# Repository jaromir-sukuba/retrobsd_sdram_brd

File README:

SDRAM board for RetroBSD
http://retrobsd.org/wiki/doku.php
http://retrobsd.org/viewtopic.php?f=3&t=5004

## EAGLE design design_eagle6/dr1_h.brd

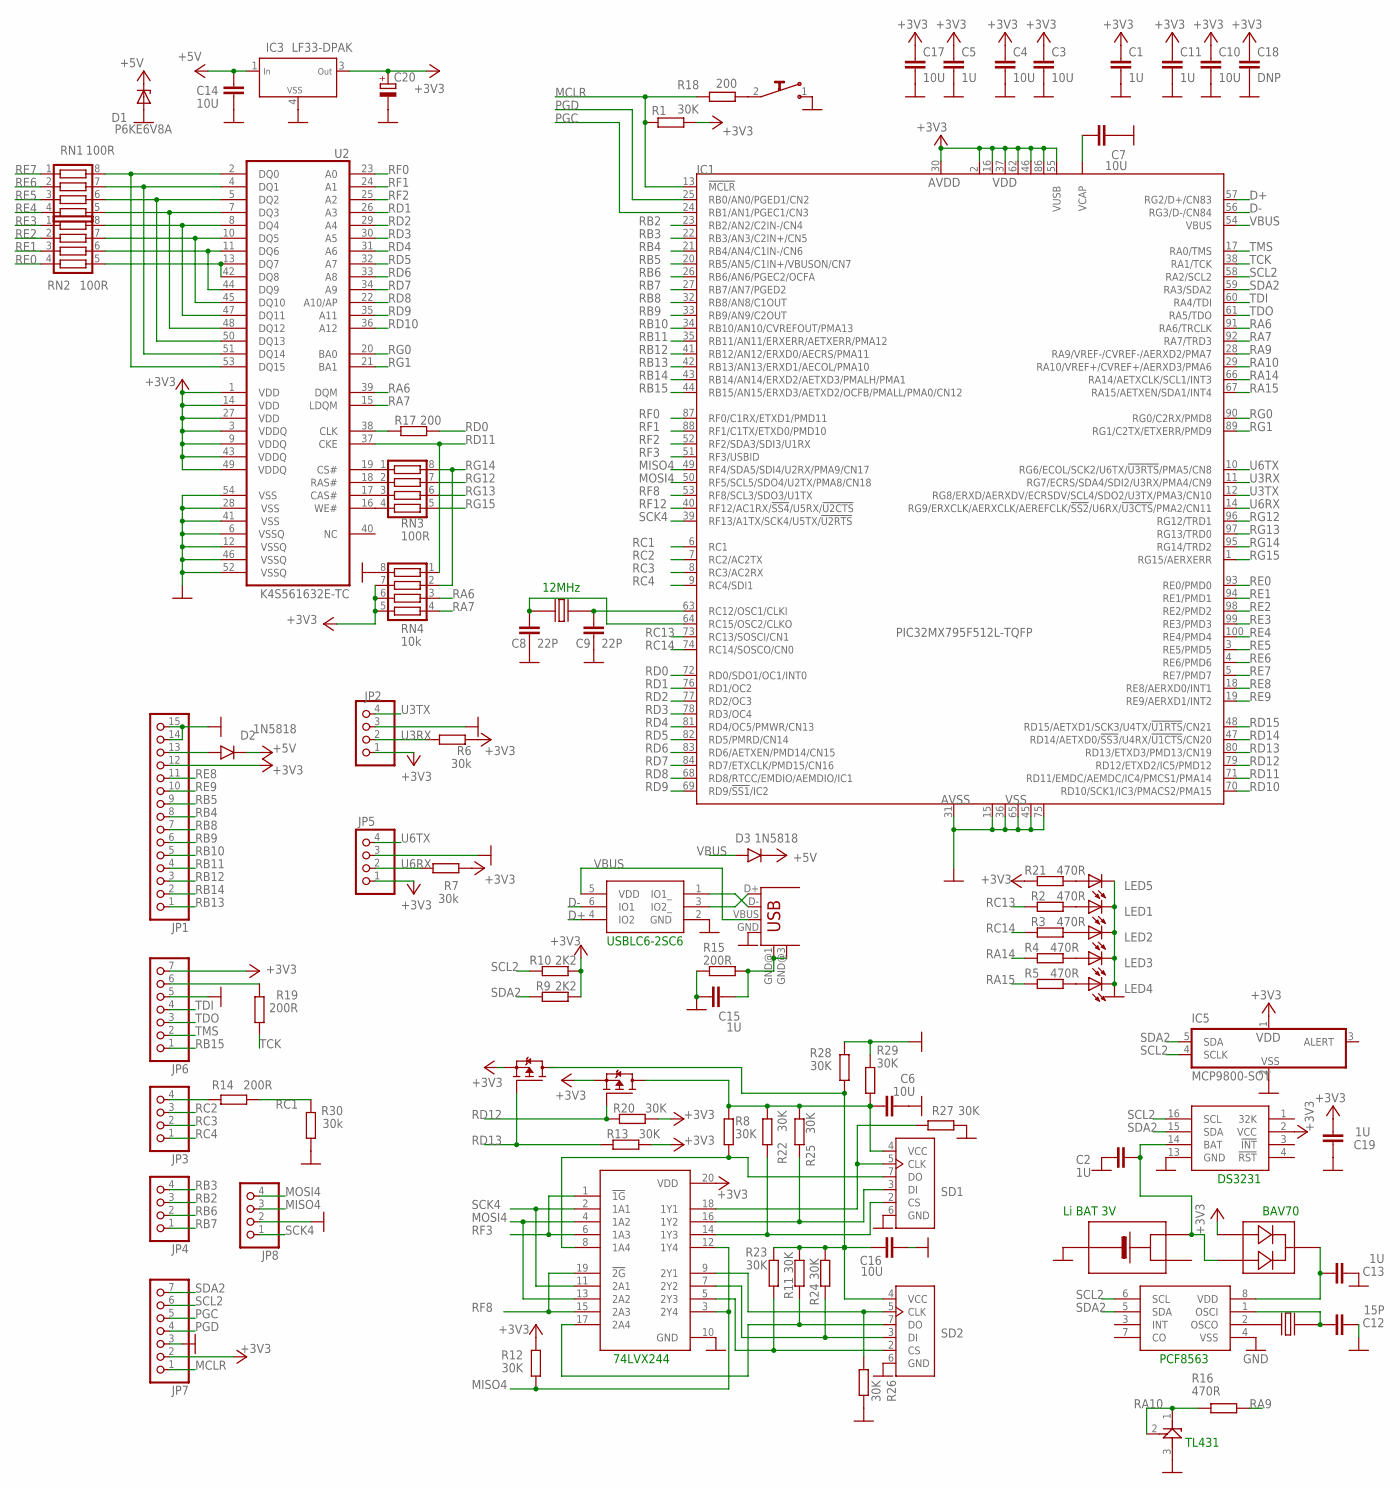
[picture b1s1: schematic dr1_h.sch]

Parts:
1: WE_TVS_2USB; SOT23-6
B1: BATT_3001; BATT_KEYS3001
C1, C2, C5, C11, C13: 1U; R0805
C3, C4, C6, C7, C10, C14, C16, C17: 10U; R0805
C8, C9: 22P; 0603
C12: 15P; R0805
C15, C19: 1U; 0603
C18: DNP; R0805
C20: CPOL-EUSMCB; SMC_B
D1: P6KE6V8A; SMB
D2, D3: 1N5818; SM-1
IC1: PIC32MX795F512L-TQFP; TQFP100
IC2: 74244TSSOP20; TSSOP20
IC3: LF33-DPAK; DPAK
IC4: PCF8563_SO8; SO-08
IC5: MCP9800-SOT; SOT23-5L
JP1: PINHD-1X15_2.54-S; 1X15-S
JP2, JP3, JP4, JP5, JP8: PINHD-1X04_2.54-S; 1X04-S
JP6, JP7: PINHD-1X07_2.54-S; 1X07-S
LED1, LED2, LED3, LED4, LED5: LEDCHIPLED_0603; CHIPLED_0603
R1, R8, R11, R12, R13, R20, R22, R23, R24, R25, R26, R27, R28, R29: 30K; 0603
R2, R3, R4, R5, R16, R21: 470R; 0603
R6, R7, R30: 30k; 0603
R9, R10: 2K2; 0603
R14, R15, R19: 200R; 0603
R17, R18: 200; 0603
RN1, RN2, RN3: 100R; CTS742C083
RN4: 10k; CTS742C083
SD1, SD2: SF-MICROSD; MICROSD
T1: SI2333; SOT23-3
U2: K4S561632E-TC; TSOP54
U$1: TL431_SOT23; SOT23
U$2: DS3231; SO-16
U$6: BAV70; SOT23
U$8: SWITCH_MINI; SW_SMD_MINI
U$12: SI2333; SOT23-3
USB1: USB-MB-S
X1: 32768; TC38
X2: 12MHz; TC38

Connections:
+3V3: C1.1, C3.1, C4.1, C5.1, C10.1, C11.1, C17.1, C18.1, C19.2, C20.+, IC1.2 (VDD1), IC1.16 (VDD2), IC1.30 (AVDD), IC1.37 (VDD3), IC1.46 (VDD4), IC1.55 (VUSB), IC1.62 (VDD), IC1.86 (VDD5), IC2.20 (VDD), IC3.3 (OUT), IC5.1 (VDD), JP1.12, JP2.1, JP5.1, JP6.7, JP7.2, R1.2, R6.1, R7.1, R9.2, R10.2, R12.2, R13.1, R20.2, R21.1, RN4.5, RN4.6, RN4.7, T1.2 (S), U2.1 (VDD), U2.3 (VDDQ), U2.9 (VDDQ), U2.14 (VDD), U2.27 (VDD), U2.43 (VDDQ), U2.49 (VDDQ), U$2.2 (VCC), U$6.1 (A1), U$12.2 (S)
+5V: C14.1, D1.C, D2.K, D3.K, IC3.1 (IN)
D+: 1.4 (IO2), IC1.57 (RG2/D+/CN83)
D-: 1.6 (IO1), IC1.56 (RG3/D-/CN84)
GND: 1.2 (GND), B1.NEG, C1.2, C2.2, C3.2, C4.2, C5.2, C6.2, C7.2, C8.2, C9.2, C10.2, C11.2, C12.2, C13.2, C14.2, C15.1, C16.2, C17.2, C18.2, C19.1, C20.-, D1.A, IC1.15 (VSS1), IC1.31 (AVSS), IC1.36 (VSS2), IC1.45 (VSS3), IC1.65 (VSS), IC1.75 (VSS4), IC2.10 (GND), IC3.4 (VSS), IC4.4 (VSS), IC5.2 (VSS), JP1.14, JP1.15, JP2.3, JP5.3, JP6.5, JP7.3, JP8.2, LED1.C, LED2.C, LED3.C, LED4.C, LED5.C, R15.1, R26.1, R27.1, R28.1, R29.1, R30.1, RN4.8, SD1.6 (GND), SD2.6 (GND), U2.6 (VSSQ), U2.12 (VSSQ), U2.28 (VSS), U2.41 (VSS), U2.46 (VSSQ), U2.52 (VSSQ), U2.54 (VSS), U$1.3 (A), U$2.13 (GND), U$8.1, USB1.GND
MCLR: IC1.13 (!MCLR), JP7.1, R1.1, R18.1
MISO4: IC1.49 (RF4/SDA5/SDI4/U2RX/PMA9/CN17), IC2.3 (2Y4), IC2.12 (1Y4), JP8.3, R12.1
MOSI4: IC1.50 (RF5/SCL5/SDO4/U2TX/PMA8/CN18), IC2.4 (1A2), IC2.13 (2A2), JP8.4
unnamed: C9.1, IC1.63 (RC12/OSC1/CLKI), X2.P$2
unnamed: JP6.6, R19.2
unnamed: IC4.2 (OSCO), X1.P$1
unnamed: IC2.18 (1Y1), R27.2, SD1.5 (CLK)
unnamed: IC2.16 (1Y2), R25.2, SD1.3 (DI)
unnamed: C12.1, IC4.1 (OSCI), X1.P$2
unnamed: LED1.A, R2.2
unnamed: LED2.A, R3.2
unnamed: LED3.A, R4.2
unnamed: LED4.A, R5.2
unnamed: C13.1, IC4.8 (VDD), U$6.3 (C)
unnamed: B1.POS2, C2.1, U$2.14 (BAT), U$6.2 (A2)
unnamed: C15.2, R15.2, USB1.GND@1 (GND), USB1.GND@3 (GND)
unnamed: D2.A, JP1.13
unnamed: C8.1, IC1.64 (RC15/OSC2/CLKO), X2.P$1
unnamed: RN2.5, U2.13 (DQ7), U2.42 (DQ8)
unnamed: RN2.6, U2.11 (DQ6), U2.44 (DQ9)
unnamed: RN2.7, U2.10 (DQ5), U2.45 (DQ10)
unnamed: RN2.8, U2.8 (DQ4), U2.47 (DQ11)
unnamed: RN1.5, U2.7 (DQ3), U2.48 (DQ12)
unnamed: RN1.6, U2.5 (DQ2), U2.50 (DQ13)
unnamed: RN1.7, U2.4 (DQ1), U2.51 (DQ14)
unnamed: RN1.8, U2.2 (DQ0), U2.53 (DQ15)
unnamed: RN3.2, U2.18 (RAS#)
unnamed: RN3.3, U2.17 (CAS#)
unnamed: RN3.4, U2.16 (WE#)
unnamed: RN3.1, U2.19 (CS#)
unnamed: R18.2, U$8.2
unnamed: R17.1, U2.38 (CLK)
unnamed: IC2.14 (1Y3), R22.1, SD1.2 (CS)
unnamed: IC2.8 (1A4), R8.2, SD1.7 (DO)
unnamed: IC2.9 (2Y1), R26.2, SD2.5 (CLK)
unnamed: C7.1, IC1.85 (VCAP)
unnamed: IC2.7 (2Y2), R24.1, SD2.3 (DI)
unnamed: IC2.5 (2Y3), R23.1, SD2.2 (CS)
unnamed: 1.1 (IO1_), USB1.D-
unnamed: LED5.A, R21.2
unnamed: JP3.4, R14.2
unnamed: IC2.17 (2A4), R11.1, SD2.7 (DO)
unnamed: 1.3 (IO2_), USB1.D+
unnamed: C6.1, R8.1, R22.2, R25.1, R29.2, SD1.4 (VCC), U$12.3 (D)
unnamed: C16.1, R11.2, R23.2, R24.2, R28.2, SD2.4 (VCC), T1.3 (D)
PGC: IC1.24 (RB1/AN1/PGEC1/CN3), JP7.5
PGD: IC1.25 (RB0/AN0/PGED1/CN2), JP7.4
RA6: IC1.91 (RA6/TRCLK), RN4.3, U2.39 (DQM)
RA7: IC1.92 (RA7/TRD3), RN4.4, U2.15 (LDQM)
RA9: IC1.28 (RA9/VREF-/CVREF-/AERXD2/PMA7), R16.2
RA10: IC1.29 (RA10/VREF+/CVREF+/AERXD3/PMA6), R16.1, U$1.1 (C), U$1.2 (R)
RA14: IC1.66 (RA14/AETXCLK/SCL1/INT3), R4.1
RA15: IC1.67 (RA15/AETXEN/SDA1/INT4), R5.1
RB2: IC1.23 (RB2/AN2/C2IN-/CN4), JP4.3
RB3: IC1.22 (RB3/AN3/C2IN+/CN5), JP4.4
RB4: IC1.21 (RB4/AN4/C1IN-/CN6), JP1.8
RB5: IC1.20 (RB5/AN5/C1IN+/VBUSON/CN7), JP1.9
RB6: IC1.26 (RB6/AN6/PGEC2/OCFA), JP4.2
RB7: IC1.27 (RB7/AN7/PGED2), JP4.1
RB8: IC1.32 (RB8/AN8/C1OUT), JP1.7
RB9: IC1.33 (RB9/AN9/C2OUT), JP1.6
RB10: IC1.34 (RB10/AN10/CVREFOUT/PMA13), JP1.5
RB11: IC1.35 (RB11/AN11/ERXERR/AETXERR/PMA12), JP1.4
RB12: IC1.41 (RB12/AN12/ERXD0/AECRS/PMA11), JP1.3
RB13: IC1.42 (RB13/AN13/ERXD1/AECOL/PMA10), JP1.1
RB14: IC1.43 (RB14/AN14/ERXD2/AETXD3/PMALH/PMA1), JP1.2
RB15: IC1.44 (RB15/AN15/ERXD3/AETXD2/OCFB/PMALL/PMA0/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), JP6.1
RC1: IC1.6 (RC1), R14.1, R30.2
RC2: IC1.7 (RC2/AC2TX), JP3.3
RC3: IC1.8 (RC3/AC2RX), JP3.2
RC4: IC1.9 (RC4/SDI1), JP3.1
RC13: IC1.73 (RC13/SOSCI/CN1), R2.1
RC14: IC1.74 (RC14/SOSCO/CN0), R3.1
RD0: IC1.72 (RD0/SDO1/OC1/INT0), R17.2
RD1: IC1.76 (RD1/OC2), U2.26 (A3)
RD2: IC1.77 (RD2/OC3), U2.29 (A4)
RD3: IC1.78 (RD3/OC4), U2.30 (A5)
RD4: IC1.81 (RD4/OC5/PMWR/CN13), U2.31 (A6)
RD5: IC1.82 (RD5/PMRD/CN14), U2.32 (A7)
RD6: IC1.83 (RD6/AETXEN/PMD14/CN15), U2.33 (A8)
RD7: IC1.84 (RD7/ETXCLK/PMD15/CN16), U2.34 (A9)
RD8: IC1.68 (RD8/RTCC/EMDIO/AEMDIO/IC1), U2.22 (A10/AP)
RD9: IC1.69 (RD9/!SS1!/IC2), U2.35 (A11)
RD10: IC1.70 (RD10/SCK1/IC3/PMACS2/PMA15), U2.36 (A12)
RD11: IC1.71 (RD11/EMDC/AEMDC/IC4/PMCS1/PMA14), RN4.1, U2.37 (CKE)
RD12: IC1.79 (RD12/ETXD2/IC5/PMD12), R20.1, U$12.1 (G)
RD13: IC1.80 (RD13/ETXD3/PMD13/CN19), R13.2, T1.1 (G)
RD14: IC1.47 (RD14/AETXD0/!SS3!/U4RX/!U1CTS!/CN20)
RD15: IC1.48 (RD15/AETXD1/SCK3/U4TX/!U1RTS!/CN21)
RE0: IC1.93 (RE0/PMD0), RN2.4
RE1: IC1.94 (RE1/PMD1), RN2.3
RE2: IC1.98 (RE2/PMD2), RN2.2
RE3: IC1.99 (RE3/PMD3), RN2.1
RE4: IC1.100 (RE4/PMD4), RN1.4
RE5: IC1.3 (RE5/PMD5), RN1.3
RE6: IC1.4 (RE6/PMD6), RN1.2
RE7: IC1.5 (RE7/PMD7), RN1.1
RE8: IC1.18 (RE8/AERXD0/INT1), JP1.11
RE9: IC1.19 (RE9/AERXD1/INT2), JP1.10
RF0: IC1.87 (RF0/C1RX/ETXD1/PMD11), U2.23 (A0)
RF1: IC1.88 (RF1/C1TX/ETXD0/PMD10), U2.24 (A1)
RF2: IC1.52 (RF2/SDA3/SDI3/U1RX), U2.25 (A2)
RF3: IC1.51 (RF3/USBID), IC2.1 (!1G), IC2.6 (1A3)
RF8: IC1.53 (RF8/SCL3/SDO3/U1TX), IC2.15 (2A3), IC2.19 (!2G)
RF12: IC1.40 (RF12/AC1RX/!SS4!/U5RX/!U2CTS)
RG0: IC1.90 (RG0/C2RX/PMD8), U2.20 (BA0)
RG1: IC1.89 (RG1/C2TX/ETXERR/PMD9), U2.21 (BA1)
RG12: IC1.96 (RG12/TRD1), RN3.7
RG13: IC1.97 (RG13/TRD0), RN3.6
RG14: IC1.95 (RG14/TRD2), RN3.8, RN4.2
RG15: IC1.1 (RG15/AERXERR), RN3.5
SCK4: IC1.39 (RF13/A1TX/SCK4/U5TX/!U2RTS), IC2.2 (1A1), IC2.11 (2A1), JP8.1
SCL2: IC1.58 (RA2/SCL2), IC4.6 (SCL), IC5.4 (SCLK), JP7.6, R10.1, U$2.16 (SCL)
SDA2: IC1.59 (RA3/SDA2), IC4.5 (SDA), IC5.5 (SDA), JP7.7, R9.1, U$2.15 (SDA)
TCK: IC1.38 (RA1/TCK), R19.1
TDI: IC1.60 (RA4/TDI), JP6.4
TDO: IC1.61 (RA5/TDO), JP6.3
TMS: IC1.17 (RA0/TMS), JP6.2
U3RX: IC1.11 (RG7/ECRS/SDA4/SDI2/U3RX/PMA4/CN9), JP2.2, R6.2
U3TX: IC1.12 (RG8/ERXD/AERXDV/ECRSDV/SCL4/SDO2/U3TX/P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), JP2.4
U6RX: IC1.14 (RG9/ERXCLK/AERXCLK/AEREFCLK/!SS2!/U6RX/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), JP5.2, R7.2
U6TX: IC1.10 (RG6/ECOL/SCK2/U6TX/!U3RTS!/PMA5/CN8), JP5.4
VBUS: 1.5 (VDD), D3.A, IC1.54 (VBUS), USB1.VBUS

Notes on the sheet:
DS3231
PCF8563
74LVX244
TL431
Li BAT 3V
BAV70
12MHz
USBLC6-2SC6

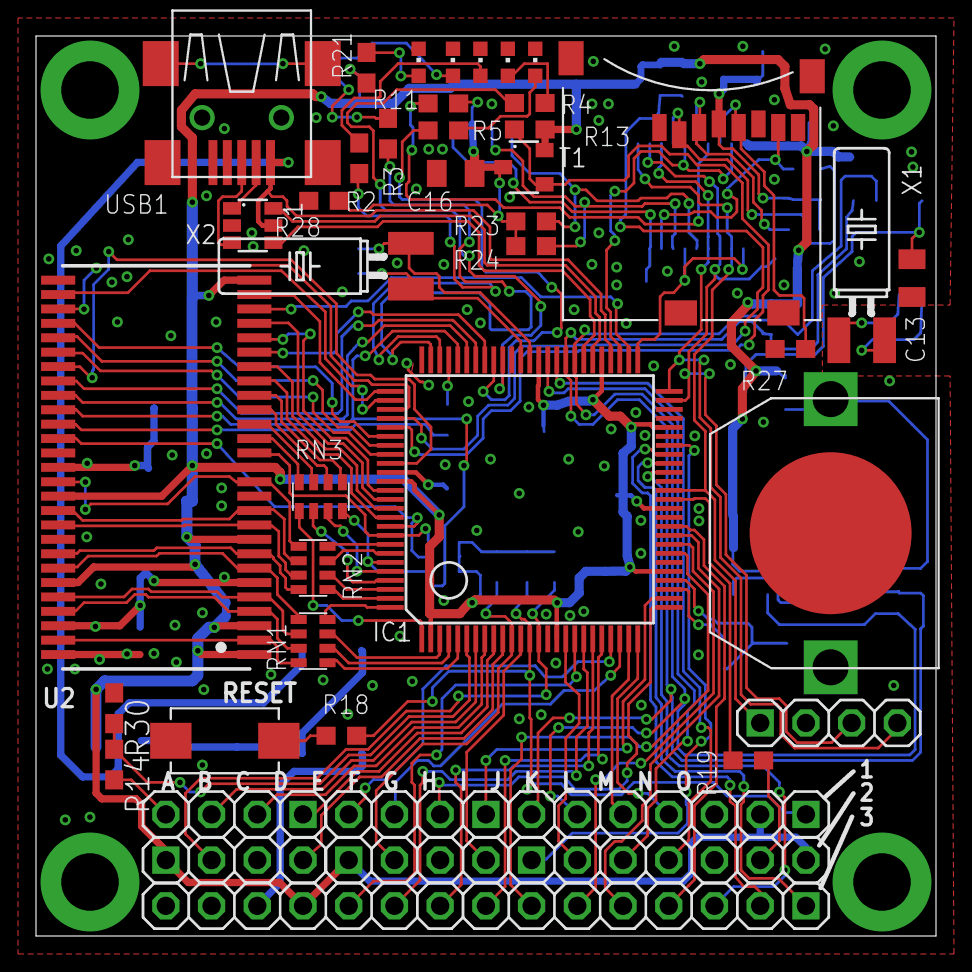
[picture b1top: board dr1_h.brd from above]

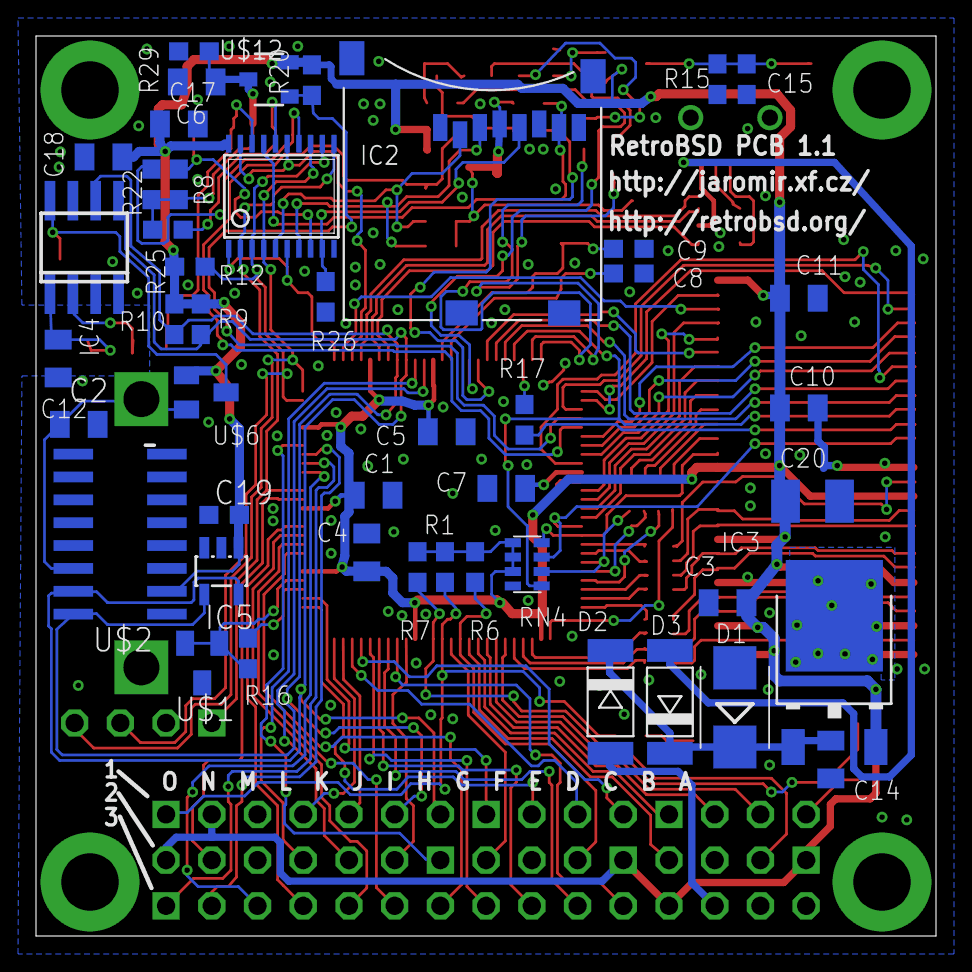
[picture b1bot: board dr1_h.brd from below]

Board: 2 copper layers, 50.0 x 50.0 mm, 89 parts (46 on the bottom side), 125 nets.

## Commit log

2014-03-18 rev 1
    initial release
2014-03-18 rev 1
